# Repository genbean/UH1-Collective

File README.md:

# Heli Collective

A 3D-printed, desk-mounted collective for helicopter flight simulators, modelled on the UH-1 "Huey". It plugs into a PC by USB and shows up as an ordinary game controller, so any sim can use it.

- **The lever** is a 25 mm carbon-fibre tube in a printed base that screws to the desk. It pivots on two ball bearings, a gas strut balances the head's weight, and a knob sets the friction. It travels 32° to a fixed stop. The lever is two-thirds as long as the real one and starts level, so your hand rises about as far as on a real Huey (9.4 in against 9.25 in).
- **The head** is the Huey's collective switch box: GOV RPM, landing light and search light toggles, the SEARCH CONT hat (an 8-way stick), the STOP REL button and the starter trigger. Under it, the twist-grip throttle turns 181° between two hard stops, idle and full open, and stays where you leave it.
- **Sensors:** two AS5600 magnetic angle sensors, one for the lever in the base and one for the throttle in the head. There are no potentiometers to wear out.
- **Electronics:** the HeliSR board, a small PCB that carries a Pro Micro, sits in the head. It reads 16 switch inputs, and the AS5600s over I²C on four sensor ports. Only the USB cable comes out of the base.
- **Software:** the HeliSR firmware and a Windows app, HeliSR Configurator. The app flashes the board, assigns each switch position to a game button and calibrates the axes. Both are based on FreeJoy.

**Interactive exploded views** (point at any part to see what it is): [the base](https://htmlpreview.github.io/?https://github.com/genbean/UH1-Collective/blob/main/Base/renders/rev4_exploded.html), [the base's lever](https://htmlpreview.github.io/?https://github.com/genbean/UH1-Collective/blob/main/Base/renders/rev4_lever_exploded.html), [the head](https://htmlpreview.github.io/?https://github.com/genbean/UH1-Collective/blob/main/Head/renders/HueyHeadR5_Exploded.html), [the head from behind](https://htmlpreview.github.io/?https://github.com/genbean/UH1-Collective/blob/main/Head/renders/HueyHeadR5_Exploded_Rear.html).

More pictures: [from the side](renders/HeliCollective_side.png) and [at the 32° stop](renders/HeliCollective_32deg.png). [`renders/HeliCollective_Assembly.glb`](renders/HeliCollective_Assembly.glb) is the whole collective in 3D; it opens in Windows 3D Viewer or any glTF viewer.

## The parts

Each folder has its own README with the details: how it works, printing, the parts it needs, assembly, and how to rebuild the files.

| Folder | What's in it |
|---|---|
| [`Base/`](Base/README.md) | **MkIII base, Rev 4.** 73 mm (2.87 in) wide, the lever centred on the tube: the pivot on thin-section bearings, the split lever, a shell that encloses it, the gas strut, the brake behind the hub, the stops and the collective's AS5600. Ready-to-print STLs, fit-test coupons, a STEP assembly, renders with every screw labelled, and the scripts that make them. |
| [`Head/`](Head/README.md) | **Huey head, Rev 5.** The switch box in one print, cut to the real UH-1 panels' dimensions, with the throttle grip and its gears, the throttle's AS5600, the starter trigger and the search light hat, and a collision check (`check_r5.py`). STLs and scripts. The BOM lists it. |
| [`PCB/HeliSR/`](PCB/HeliSR/README.md) | **HeliSR Rev 4.0 board.** Sixteen switch inputs, and four I²C ports for the AS5600s, through a PCA9546A switch, in place of the analog inputs. KiCad files, Gerbers, connector pinouts, how to prepare the AS5600 modules, and the assembly order. |
| [`PCB/SearchHat/`](PCB/SearchHat/README.md) | **SearchHat Rev 1.0: the SEARCH CONT hat's breakout board.** An ALPS RKJXM1015004 8-direction stick switch on a 22 × 29 mm board that screws to the lower panel's back, with a JST SH socket or wire pads. KiCad files, Gerbers, the pinout and how to build it. |
| [`BOM/`](BOM) | **The bill of materials for the whole collective:** [`Heli_Collective_BOM.xlsx`](BOM/Heli_Collective_BOM.xlsx): every part to buy, with part numbers, where it goes, where to buy it, how many and the price, and a sheet of the printed parts. [`tools/make_bom.py`](tools/make_bom.py) rewrites it (and checks the board's parts against the board file). |
| [`Software/`](Software/README.md) | **HeliSR firmware and HeliSR Configurator**, with their documentation in [`Software/docs/`](Software/docs) and example profiles, including one for this collective. |
| [`renders/`](renders) | Pictures and a 3D model of the complete collective: head Rev 5 on base Rev 4. [`Base/make_renders_r4.py`](Base/make_renders_r4.py) builds them, and base Rev 4's renders, exploded view and screw chart. [`make_diagrams.py`](renders/make_diagrams.py) draws the head's exploded views, screw maps and screw chart from that model. |

## What you need

The full list, with quantities, part numbers, links and prices, is the [BOM spreadsheet](BOM/Heli_Collective_BOM.xlsx). In outline:

**Electronics**
- The HeliSR Rev 4.0 PCB: send [`HeliSR_Rev4.0_Gerbers.zip`](PCB/HeliSR/HeliSR_Rev4.0_Gerbers.zip) to any PCB maker (2 layers, 39.3 × 33.6 mm).
- The SearchHat Rev 1.0 PCB, for the SEARCH CONT hat: send [`SearchHat_Rev1.0_Gerbers.zip`](PCB/SearchHat/SearchHat_Rev1.0_Gerbers.zip) the same way (2 layers, 22 × 29 mm). Its ALPS switch and JST socket are in the BOM.
- The parts that solder onto it, all from Mouser: the BOM lists them with their board positions.
- A **5 V / 16 MHz Pro Micro** (ATmega32U4). This build uses a USB-C clone; the 3.3 V / 8 MHz version isn't supported.
- Two AS5600 magnetic angle sensor modules, with their magnets.
- JST SR 1.0 mm cables for the board, a 4-core lead for the base's sensor (SDA, GND, VCC, SCL), and a USB-A to USB-C cable. The USB cable runs up through the base and the tube and is spliced inside the head; the BOM's notes explain how.

**Head**
- Four APEM 600H toggle switches, a Same Sky PB4 push button a TE 6 × 6 mm tact switch for the starter trigger, and an ALPS RKJXM1015004 8-way stick switch for the SEARCH CONT hat.
- Four 24 × 2 mm nitrile O-rings, which the throttle grip turns on, a pen spring and four 4 mm board spacers.

**Base**
- Two 6808-2RS thin-section ball bearings (40 × 52 × 7 mm), a 6 in (152 mm), 45 N gas strut with eyelet ends, and a 25 × 23 mm roll-wrapped carbon tube, 500 mm long, used whole.

**Screws, consumables and tools**
- Every screw and nut comes from MonsterBolts in packs of 10, about $23 in all: black-oxide hex socket screws, M2 Phillips flat heads, a stainless M5 hex bolt and plain steel nuts. The BOM and each part's README list them.
- Grease for the bearings and the O-rings, CA glue, hot glue and blue thread-locker; M2, M3, M4 and M5 taps, and 4 mm and 5.2 mm drills for the tube; a soldering iron that can handle 1.0 mm pitch SMD parts.

**Printing and a PC**
- An FDM printer with about 180 mm of build height. The tallest part, the throttle grip, is 173 mm printed upright. The head's panel labels are white, printed in a second filament for the first three layers (an AMS, or a filament change).
- A PC with 64-bit Windows 10 or 11 to set the board up. After that it's a standard USB game controller.
- Python, only if you change the CAD. The STLs are ready to print, and each part's README lists what its scripts need.

## Build order

Each step points to the README that covers it.

1. **Order the parts** from the [BOM](BOM/Heli_Collective_BOM.xlsx), and the PCBs from the Gerbers.
2. **Print the fit-test coupons first**, with the filament and settings you'll use, and try them on your carbon tube, bearings, sensor modules and printed lever dowels: [the base's coupons](Base/README.md#fit-test-coupons) (the 6808 bearing fits, the lever's dowel holes and the tube socket), and the head's O-ring and sensor seat coupons (printed as in [Head, Printing](Head/README.md#printing)). If a fit is off, change its setting in the script and rebuild the STLs.
3. **Build the HeliSR board** ([assembly order](PCB/HeliSR/README.md#assembly-order)) and fit the Pro Micro.
4. **Flash and test it** with HeliSR Configurator: the [quick start](Software/docs/quick-start.md) goes from a bare Pro Micro to a working controller. Check every input now, before it goes into the head. The app picks the HeliSR firmware for you.
5. **Prepare the two AS5600 modules:** remove R1 and R4, wire DIR (to VCC on the base's sensor, to GND on the throttle's), check for about 1 µF on VDD3V3, and measure the module's pull-ups. See the Rev 4.0 board's [AS5600 modules](PCB/HeliSR/README.md#as5600-modules).
6. **Print and assemble the base** ([Base Rev 4, Assembly](Base/README.md#assembly)). The USB cable and the sensor lead go into the lever halves before you close them, the brake strap goes in before the lever, and the tube is drilled, notched and fitted at the end.
7. **Print and assemble the head** ([Head, Assembly](Head/README.md#assembly)): the throttle parts, the starter trigger, the grip on the tube, the head pressed onto the tube, then the board, switches and panels.
8. **Set the two AS5600s' ranges** in HeliSR Configurator's AS5600 helper ([AS5600 guide](Software/docs/as5600.md#setting-the-start-and-stop)): the collective on AX1, the throttle on AX4. The firmware writes each range to its sensor over I²C at every start-up and burns nothing, so it can be set again whenever you like.
9. **Balance and set the friction** ([Base Rev 4, Balance](Base/README.md#balance) and [Brake](Base/README.md#brake)).
10. **Load the UH-1 profile** in HeliSR Configurator, calibrate the axes, and bind the buttons in your sim ([Profiles](Software/docs/profiles.md#uh-1-collective-helisr-head)).

## Status

As of November 2026 the current design is **head Rev 5, base Rev 4 and HeliSR Rev 4.0**.

- **First build:** the first collective was printed and assembled on base Rev 3. What it taught us went into base Rev 4:
  - **Bearings:** the bearing seats fitted perfectly, and the races pressed onto the trunnions a hair too tight.
  - **Strut:** the 45 N strut lifted the lever. Its anchor has since moved, in Rev 4.
  - **Width:** at 130 mm, the base was wider than it needed to be.
- **Base Rev 4:** its first frame, shell and lever were printed and assembled (2026-11-08), and the bearing coupons fitted. Since then it has changed (split lever, brake strap, covers, cable path, lever opening), checked in CAD for collisions and fits through the whole travel and the assembly order; reprint all of it but the strut collar.
- **Head Rev 5:** designed, and checked in CAD for collisions and fits. Earlier head fits were tuned with coupons on an aluminium tube, so check them on the carbon tube.
- **HeliSR Rev 4.0 board:** designed and checked (design rules, and every pad's net against the chips' datasheets), not built yet.
- **Software:** the firmware and HeliSR Configurator in [`Software/`](Software/README.md) support the Rev 4.0 board, with its I²C sensors and their ranges set in the app. They are tested on the PC and a bare Pro Micro only; the Rev 4.0 sensor code against a model of the I²C switch and the AS5600. The software hasn't run on a built board with real switches and sensors.

Expect more changes as the build goes on.

## Credits and licence

- This repository is under the **GNU General Public License v3.0** ([LICENSE](LICENSE)), except where a folder says otherwise.
- **The software in `Software/`** is under the **GNU GPL v3 or later**. It is a modified version of [FreeJoy](https://github.com/FreeJoy-Team/FreeJoy) and [FreeJoyConfiguratorQt](https://github.com/FreeJoy-Team/FreeJoyConfiguratorQt) by the FreeJoy team, ported to the Pro Micro, and isn't made or supported by them. [`Software/NOTICE.md`](Software/NOTICE.md) lists the changes and the third-party components.
- **The original collective: Gazmac52.** This project grew out of [DIY Helicopter Collective Hall Effect](https://www.thingiverse.com/thing:5226353) by **Gazmac52** on Thingiverse, the "MkII" in this project's file names, licensed under [Creative Commons Attribution 4.0](https://creativecommons.org/licenses/by/4.0/). Several components are borrowed from it: the head's throttle grip is built from its grip, modified (`Head/source/MkII-Grip-bore-relieved-25mm.stl`), the HeliSR board reads its switches through 74HC165 shift registers, as Gazmac52's board does, and the head and base are modelled in the MkII's coordinate frames.
- **hotpretzel.** Some components are borrowed from [UH-1 Huey Helicopter Collective](https://www.thingiverse.com/thing:4284120) by **hotpretzel** on Thingiverse, licensed under [Creative Commons Attribution-NonCommercial](https://creativecommons.org/licenses/by-nc/4.0/). The head's faux throttle friction knob is built from hotpretzel's friction knob STL: its wheel profile and flutes were measured off it. So the knob, and the head bodies that carry it (`HueyHeadR4-Body.stl`, `HueyHeadR5-Body.stl` and the scripts' `friction_knob()`), are for **non-commercial use only**, whatever the licence of the folder they're in.
- **Font:** the panels' labels are cut from **Routed Gothic Narrow** by Darren Embry ([webonastick.com/routed-gothic](https://webonastick.com/routed-gothic/)), a digitized Leroy lettering template and the closest free match to the engraved lettering on the real UH-1 panels. It's bundled in [`fonts/routed-gothic/`](fonts/routed-gothic) under the [SIL Open Font License 1.1](fonts/routed-gothic/LICENSE.md), so the panels rebuild on any system.
- **The real UH-1's dimensions:** **Kornskydiver**'s caliper photos of a real UH-1 head (2017) and **dcval**'s scaled drawing of its panels (2025), from the ED Forums thread [Huey Collective Measurements](https://forum.dcs.world/topic/152333-huey-collective-measurements/). Head Rev 5 is built to them. Copies are in [`Head/reference/`](Head/reference/README.md), with credit; they belong to their authors and aren't covered by this repository's licence.

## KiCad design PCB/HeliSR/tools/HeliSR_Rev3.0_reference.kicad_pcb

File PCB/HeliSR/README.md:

# HeliSR Rev 4.0 – Pro Micro + I²C collective board (Huey head)

> **Designed, not ordered, not built.** The HeliSR firmware has a Rev 4.0 build and HeliSR Configurator supports
> the board, but neither has run on one yet. See [Firmware](#firmware).

A small carrier board for the collective's switch box: a **SparkFun Pro Micro 5V/16 MHz** with **16 switch
inputs** read through two 74HC165 shift registers, and **four I²C ports for AS5600 magnetic angle
sensors**.

The board reads each AS5600's angle digitally over I²C, which doesn't pick up noise on a long cable the way an
analog output does. Every AS5600
has the same I²C address (0x36), so a **PCA9546A I²C switch** on the back of the board gives each port its own
channel, and the firmware talks to one sensor at a time. Each port has its own 2.2 kΩ pull-ups, and all four
ports are built the same, so any port takes a short or a long cable.

| | |
|---|---|
| Board size | 39.3 × 33.64 mm (1.55 × 1.32 in), with four M3 holes. 2 layers, 1.6 mm FR4 |
| Parts | Connectors, the button, the Pro Micro sockets, the shift registers and their parts on the **front**; the I²C switch, its capacitor and all the resistors on the **back**. Every resistor and capacitor is **1206**, for hand soldering |
| Switch inputs | 16, on two 10-pin JST SR/SH 1.0 mm connectors (BM10B-SRSS-TB, SMD) |
| AS5600 ports | 4, each on its own 4-pin JST SR/SH 1.0 mm connector (BM04B-SRSS-G-TB, SMD): **1 SDA, 2 GND, 3 VCC, 4 SCL** |
| I²C switch | PCA9546A (TI PCA9546ADR, SOIC-16 narrow), address 0x70, with its /RESET on a Pro Micro pin |
| Pull-ups | 2.2 kΩ on SDA and SCL of each port (R1–R8); 10 kΩ on the Pro Micro's SDA and SCL (R9, R10) and on /RESET (R11) |
| Button | **RST** (SW1, E-Switch TL1015AF160QG). No PROG buttons: over I²C the firmware sets each sensor's range itself |
| Ground | Both layers poured with ground and stitched together (see [Checks](#checks-done-on-this-revision)) |
| Fab specs | Cheap-fab rules: 0.2 mm clearance, 0.2 mm signal and 0.3 mm VCC/GND tracks, 0.6/0.3 mm vias, holes at least 0.6 mm apart |

Pots and Hall sensors can't go on the AX ports. The Pro Micro still has analog-capable pins free (A2, A3,
4, 6, 8, 9, 10); using one means soldering a wire to the Pro Micro.

## Layout

Viewed from the top, with the USB end on the left:

- **Pro Micro** on two 12-pin sockets, its USB end at the left edge: pins 13–24 (J8) along the top, pins 1–12
  (J7) along the bottom.
- **Under it**: RN1, then C1 | U1 | C3 | U2 | C2, then RN2.
- **Top edge:** J1 (inputs 1-8), AX3 (J13).
- **Bottom edge:** J2 (inputs 9-16), AX1 (J11).
- **Far end (right):** AX4 (J14, top), RST (SW1, middle), AX2 (J12, bottom).
- **Back:** U3 under the far half of the Pro Micro with C4 beside its VCC pin, R9 and R10 beside its SDA and SCL,
  R11 beside its /RESET; under each port, that port's pair of pull-ups.

Every connector's pins face the board's middle. The JST plugs go in from the top and the cables leave upwards.

Mounting hole centres, in mm from the board's top-left corner (USB end left, J1 up): (3.2, 3.2), (36.1, 3.2),
(3.2, 30.44) and (36.1, 30.44).

## In the Huey head

It fits head Rev 4 and Rev 5 on their spacers and screws. The parts on its front are JST SH height (head Rev 5's
`check_r5.py` takes them as 4.5 mm); the parts on its back (1.75 mm at most) sit in the 4 mm gap the spacers leave
behind the board.

Two things to allow for:
- **AX4 and AX2 are at the far end**: the top of the board in the head, just below the upper
  box's toggles. Their plugs go in from the front, like the others. Leave the wires room to turn there.
- **The throttle's AS5600 needs four wires**, and so does the collective's, which runs up the tube
  from the MkIII base (`Base`). Check the wire channels take four wires.

## Connectors

**J1 (inputs 1-8) and J2 (inputs 9-16)**: 10-pin JST SR/SH 1.0 mm.

| Pin | 1 | 2 | 3 | 4 | 5 | 6 | 7 | 8 | 9 | 10 |
|---|---|---|---|---|---|---|---|---|---|---|
| J1 | GND | IN1 | IN2 | IN3 | IN4 | IN5 | IN6 | IN7 | IN8 | GND |
| J2 | GND | IN9 | IN10 | IN11 | IN12 | IN13 | IN14 | IN15 | IN16 | GND |

Each switch goes between its input pin and GND. The inputs have 10 kΩ pull-ups on the board.

**AX1–AX4 (J11–J14)**: 4-pin JST SR/SH 1.0 mm.

| Pin | 1 | 2 | 3 | 4 |
|---|---|---|---|---|
| AX1–AX4 | SDA | GND | VCC (5 V) | SCL |

The order keeps SDA and SCL apart, with GND beside SDA and VCC beside SCL, which is what you want on a long cable:
twist SDA with GND and SCL with VCC, or use a 4-core cable with those pairs. It is **not** the Qwiic / STEMMA QT
order, on purpose: those boards are 3.3 V and this port is 5 V.

If you make a lead by cutting a pre-made JST SR/SH jumper in half, find which wire is pin 1 with a meter before
soldering the sensor end: the plug is keyed, but the wires may all be one colour.

| Port | Connector | PCA9546A channel | Pull-ups (SDA, SCL) | Suggested use |
|---|---|---|---|---|
| AX1 | J11 | 2 | R1, R2 | Collective (AS5600 in the MkIII base) |
| AX2 | J12 | 1 | R3, R4 | Spare |
| AX3 | J13 | 3 | R5, R6 | Spare |
| AX4 | J14 | 0 | R7, R8 | Throttle (AS5600 in the Huey head) |

The channels follow the board's geometry, not the port numbers: the firmware maps them.

## The I²C circuit

```
Pro Micro "2" SDA ──┬── R9 10k ── VCC                    ┌── R(odd) 2.2k ── VCC
Pro Micro "3" SCL ──┼── R10 10k ── VCC        PCA9546A   ├── port pin 1 SDA ─── AS5600 SDA
Pro Micro "A1" ─────┴── R11 10k ── VCC   ──── SDA/SCL ── SDn/SCn (n = 0..3) ── port pin 4 SCL ─── AS5600 SCL
                                         /RESET, A0-A2 = GND (0x70)           └── R(even) 2.2k ── VCC
```

- **Address:** A0–A2 are tied to GND, so the switch is at **0x70**; the AS5600s are at 0x36 behind it.
- **One channel at a time:** the firmware writes the switch's control register to connect one port, reads that
  sensor, and moves on. Only that port's cable is on the bus, so the long cables don't add up.
- **Pull-ups:** each port has its own 2.2 kΩ pair, on the switch's side of its cable, so each channel is a complete
  I²C bus whether or not the sensor module has pull-ups. With the Pro Micro's 10 kΩ pair in parallel, a low SDA
  sinks 2.3 + 0.5 = 2.8 mA at 5 V, plus whatever the module's own pull-ups add. The weakest part on the bus is the
  PCA9546A, and only while it acknowledges its own writes: TI rates it to sink at least 3 mA at 0.4 V and 6 mA at
  0.6 V (SCPS148I). Every input on the bus reads below 1.5 V (0.3 × 5 V) as low, so anything up to 6 mA works with
  margin. The AS5600 sinks 20 mA at 0.4 V (ams datasheet v1-06), the ATmega32U4 more.
- **/RESET:** R11 holds it high, so the switch works even before the firmware drives A1. Pulling A1 low resets the
  switch (all channels off), which frees a stuck bus. R11 goes to the same 5 V as the chip, as TI's errata ask.
- **Clock speed:** the AS5600 runs up to 1 MHz, but long cables want a slow clock. Plan on **100 kHz**, and less
  (50 or 25 kHz) if a long cable gives errors. Even at 25 kHz, reading all four sensors takes about 10 ms. The clock
  is set in the firmware, not on the board.
- **Cable length:** the limit is the capacitance on each line: 400 pF in the I²C standard (the AS5600 allows
  550 pF). Typical 4-core cable is 50–150 pF per metre, so a metre or more is within it. With 2.2 kΩ and 200 pF
  the rise time is about 0.4 µs, well inside 100 kHz's 1 µs.

## AS5600 modules

For the common WWZMDiB module (23 × 23 mm, Amazon B0CM3C8KFT), running on the Pro Micro's 5 V:

The R numbers in this list are the module's, not the board's. The pin facts are from the AS5600 datasheet (ams
v1-06); which part on the module is R1 or R4 is from the module itself, so check yours.

- **Remove the module's R1**, the 0 Ω link between VDD5V and VDD3V3: it puts 5 V on the chip's
  3.3 V pin, whose absolute maximum is 4.0 V. The two pins are tied together only when the chip runs on 3.3 V.
- **Check there is about 1 µF from VDD3V3 to GND.** On 5 V, VDD3V3 is the output of the chip's internal regulator,
  and the datasheet asks for a 1 µF low-ESR ceramic there. A module built to run on 3.3 V through R1 may have only
  100 nF on that pin, or nothing. If so, add a 1 µF ceramic between VDD3V3 and GND.
- **Wire DIR** to GND or VCC (it floats on this module, and the chip has no pull on it). Over I²C it still sets
  which way the angle rises (GND = clockwise, seen from the chip's top face); the firmware can invert an axis
  either way.
- **Remove the module's R4**, the 1 kΩ from PGO (GPO on the module) to GND. With it fitted PGO is low, which
  selects OUT-pin programming. In that mode, pulling OUT to GND for 100 ms twice burns the
  range into the chip for good, which can be done only once; a stray short on OUT could do it by accident. Without
  R4 the chip's internal pull-up holds PGO high and OUT is just an output. Leave OUT unconnected.
- **Wire VCC, GND, SDA and SCL** to the port: pin 1 SDA, 2 GND, 3 VCC, 4 SCL.
- **Check the module's own pull-ups.** The AS5600 has none of its own; the module may add some (ams suggests
  4.7 kΩ). With the module unpowered and unplugged, measure the resistance from SDA to VCC and from SCL to VCC. The
  limit is the 6 mA in [The I²C circuit](#the-i²c-circuit):
  - **Open circuit (no reading):** no pull-ups. Fit 2.2 kΩ for the board's R1–R8 as listed.
  - **10 kΩ or 4.7 kΩ:** fine; with the board's 2.2 kΩ the bus sinks 3.3 or 3.8 mA. They also speed up the
    rising edges on a long cable. Leave them, and fit R1–R8 as listed.
  - **Under 2 kΩ:** too strong together with 2.2 kΩ. Remove the module's two pull-ups.
  - Check also that the module's pull-ups go to VCC, not to the chip's 3.3 V pin; if they read open to VCC but
    about the same value to VDD3V3, remove them, as they'd push current from the 5 V bus into the chip's regulator.

Nothing is burnt into the chip: the firmware writes each sensor's start and stop angles (ZPOS, MPOS) to its
working registers every time it starts, so the range can be changed as often as you like.

## Pro Micro pins

| Socket pin | Pro Micro pin | Port | Use |
|---|---|---|---|
| 5 | 2 | PD1 | I²C SDA |
| 6 | 3 | PD0 | I²C SCL |
| 15 | 14 | PB3 | Shift register data (U2 QH) |
| 16 | 15 | PB1 | Shift register clock |
| 17 | A0 | PF7 | Shift register load (SH/LD) |
| 18 | A1 | PF6 | PCA9546A /RESET |
| 21, 22, 3/4/23 | VCC, RST, GND | | |

Spare (not connected): TX, RX, 4, 5, 6, 7, 8, 9, 10, 16, A2 and A3. The shift-register pins are the hardware SPI
clock (15) and MISO (14), so a future firmware can read the chain with the SPI unit; pin 16 (MOSI) is then not
free for other use.

## Firmware

The HeliSR firmware in `Software/firmware/HeliSR` is built for this board by `Software/firmware/build.ps1`,
shipped as `firmware\HeliSR_Rev4.0_16MHz.hex`. It:

- reads the shift registers on pins 14 (data), 15 (clock) and A0 (load);
- runs the TWI on pins 2 and 3 at 100 kHz, or 50, 25 or 10 kHz for long cables (set in HeliSR Configurator), connects
  one port's PCA9546A channel at a time and reads its AS5600's ANGLE register (address 0x36), scaled to the analog
  inputs' 0–4092. It also reads STATUS, RAW ANGLE and AGC, for the magnet checks and the Configurator's helper;
- writes each sensor's start and stop to its volatile ZPOS and MPOS at start-up, 1 ms apart, from settings it keeps
  in EEPROM (the Configurator sets them), and CONF as 0 (the chip's factory settings, over anything burnt in); reads
  them back, and writes them again to a sensor that comes back after an error or has lost them. It never burns
  anything;
- maps channels 2, 1, 3, 0 to AX1–AX4 as above. A stuck bus is freed by pulling A1 low (never driving it high), clocking
  out a half-sent byte and sending a STOP; a port that stuck it is left alone for 250 ms;
- treats A2 and A3 as spare analog pins (axis sources 9 and 10), and leaves pin 14 out of the
  spare pins;
- sets the JTD bit in MCUCR at start-up (written twice, as the ATmega32U4 requires). A0 and A1 are also the JTAG
  pins TDI and TDO (PF7, PF6); SparkFun ships the Pro Micro with JTAG off in its fuses (high fuse 0xD8), but a clone
  with JTAG on would otherwise keep both pins from working as plain I/O.

The sensor code is tested on a PC against a model of the PCA9546A and the AS5600 (`Software/firmware/test/host`).
Nothing of this board's firmware has run on the board itself: the shift-register pins, the I²C timing on real
cables, the bus recovery and the sensors' behaviour all wait for one. `Software/PLAN.md` lists what's still to check.

**Only this board.** The firmware is for Rev 4.0 only. Every build carries a tag saying so, INFO reports it, and HeliSR Configurator refuses a `.hex` tagged for another board and asks before flashing an untagged one or a Pro Micro whose firmware reports another board.

## Files

| File | What it is |
|---|---|
| `HeliSR_Rev4.0.kicad_pcb` / `.kicad_pro` | KiCad 9 board |
| `HeliSR_Rev4.0.kicad_dru` | Custom DRC rules for the intentional overlaps (see below) |
| `HeliSR.pretty/`, `fp-lib-table` | Project footprint library: the TL1015AF160QG button footprint |
| `HeliSR_Rev4.0_Gerbers.zip` | Gerbers + drill files |
| `HeliSR_Rev4.0_Top.png`, `HeliSR_Rev4.0_Bottom_mirrored.png` | Board renders |
| `HeliSR_Rev4.0_Input_Map.csv` | Every input → connector pin → chip pin → shift order |
| `tools/` | The scripts that build, route, finish, check and export this board (see Rebuilding) |

## Assembly order

1. **The back first**, while the front is still flat: **U3** (pin 1 dot toward the far end, at the J1 side), then
   **C4** and **R1–R11** (all 1206). R1–R8 are all 2.2 kΩ; R9–R11 10 kΩ.
2. On the front, **U1, U2**, then the 1206 caps **C1, C2, C3**.
3. **RN1, RN2**. The dot (pin 1) goes in the square pad.
4. The JST headers and the RST button.
5. The two Pro Micro sockets last. Use low-profile headers for the sockets and for the Pro Micro's pins (the BOM lists a set): standard ones stand too tall for the USB cable in the head.

## Pro Micro RP2040 compatibility

Every pin the board uses is also there on the **SparkFun Pro Micro RP2040**, whose VCC pin is 3.3 V:
its pins 2 and 3 (GPIO2, GPIO3) can be the RP2040's I2C1 SDA and SCL, and the pull-ups then go to 3.3 V, which suits an AS5600 module
run in its 3.3 V mode (R1 left fitted). There is no RP2040 build of the HeliSR firmware. Not tried.

## DRC rules

`HeliSR_Rev4.0.kicad_dru` covers the intentional overlaps, each rule naming the exact footprint pairs:

- Parts nested under the Pro Micro (resistor networks, shift registers and caps between the sockets).
- The connector rows: the courtyards of J1 and AX3 (J13), and of J2 and AX1 (J11), overlap; the housings don't.
- The M3 holes: their courtyards (6.9 mm across) overlap J1, J2 and the far-end ports AX4 (J14) and AX2 (J12). Every
  pad, track and via is at least 3.5 mm from each hole centre, clear of the M3 nut's corners (3.18 mm) on the front
  and the 6.4 mm spacer on the back.
- The far end: RST's courtyard overlaps the AX4 and AX2 ports' by up to 0.3 mm; the switch body and the JST housings
  are about 1.4 mm apart.
- Library silkscreen outlines that touch where parts nest.

The rules use `(severity ignore)`, because `kicad-cli` 9.x still reports `(severity exclusion)` rules as errors
(KiCad issue 24264).

## Rebuilding

The board is generated, autorouted and finished by scripts in `tools/`, run with KiCad 9 (its own Python, which has
numpy and PIL) and Freerouting 2.5.0 on a Java 25 runtime. No other Python packages are needed. The board's parts are in
the collective's BOM, [`../../BOM`](../../BOM).

1. `gen_v4.py` places the parts, sets the nets, outline and mounting holes, and exports a DSN. The placement used
   here is `rev40_params.json`.
2. `route_v4.py` runs the generator for a list of placement variants, gives VCC/GND a 0.3 mm class, routes with
   Freerouting, imports the result (`imp_v2.py`) and DRCs it. It routes with the vias 0.7 mm across, so their holes
   end up at least 0.6 mm apart, and imports them at 0.6 mm. This board is the best of the 45 variants in the final sweep
   (U3's position, the pull-ups' offset under the ports, the far-end ports' spacing): complete, 44 router vias.
3. `finish_all_v4.py` widens the router's neck-downs, pours GND on both layers, adds GND stitching vias
   (`stitch_v4.py`), writes the DRC rules and title block (`finish_v4.py`), places the silk labels on both sides
   (`silk_fix_v4.py`), and DRCs the result.
4. `verify_netlist_v4.py` checks the netlist against the reference board and input map kept in `tools/` for it, and
   against the PCA9546A datasheet's pinout, and writes the input map.
5. `export_v4.py` writes `HeliSR_Rev4.0_Gerbers.zip` and the two renders. `tools/make_bom.py` (at the repo root) then rewrites the
   BOM (it stops if the board's parts and its list disagree).

## Checks done on this revision

- **KiCad 9 DRC:** 0 violations and 0 unconnected items at every severity (with `HeliSR_Rev4.0.kicad_dru`).
- **Netlist:** checked pad by pad by `verify_netlist_v4.py`. J1, J2, U1, U2, RN1, RN2, C1–C3 and SW1 are on the
  same nets as in the reference board, so the inputs and their shift order are unchanged. U3's pins match the
  PCA9546A datasheet (TI SCPS148I): A0 1, A1 2, /RESET 3, SD0–SC1 4–7, GND 8, SD2–SC3 9–12, A2 13, SCL 14, SDA 15,
  VCC 16. Every port, pull-up and Pro Micro pin is as listed above, and every net joins at least two pads.
- **Clearance:** the cheap-fab rules above. All copper is at least 0.5 mm from the edge, and every track and via at
  least 3.7 mm from a hole centre (every pad 4.1 mm). No neck-downs: every signal track is 0.2 mm and every VCC/GND
  track 0.3 mm.
- **Routing:** 998 mm of track, 78 vias: 44 from the router and 34 GND stitching vias. The I²C lines from U3 to the
  ports are 6–29 mm long.
- **Decoupling:** C4's VCC pad is 2.65 mm from U3's VCC pin (centre to centre); C1's is 1.8 mm from U1's and C2's
  2.7 mm from U2's.
- **Silkscreen:** every label is 1.0 mm tall with a 0.16 mm stroke, outside every courtyard on its side, and at least
  0.5 mm from the next label. The front names the connectors (J1, J2, AX1–AX4), RST, USB and the front parts; the
  back names U3, C4, R1–R11 and the board.
- **Not checked:** nothing has been built. The I²C circuit and the cable lengths are as calculated in the
  I²C section above, not measured.

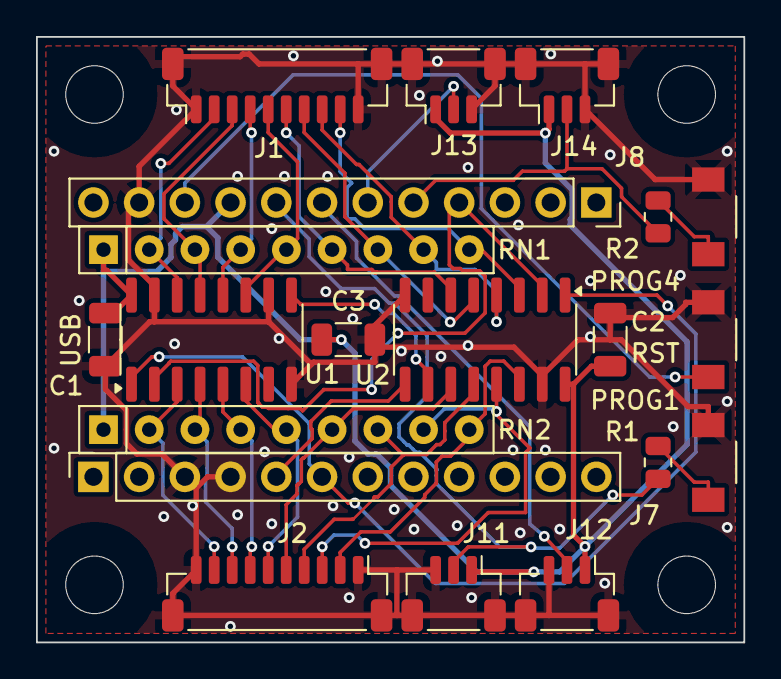
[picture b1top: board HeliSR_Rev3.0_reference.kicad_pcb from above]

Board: 2 copper layers, 39.3 x 33.6 mm, 24 parts (0 on the bottom side), 29 nets.

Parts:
C1, C2: 100nF; C_1206_3216Metric
C3: 22uF; C_1206_3216Metric
H1, H2, H3, H4: M3; MountingHole_3.2mm_M3
J1: Inputs 1-8; JST_SH_BM10B-SRSS-TB_1x10-1MP_P1.00mm_Vertical
J2: Inputs 9-16; JST_SH_BM10B-SRSS-TB_1x10-1MP_P1.00mm_Vertical
J7: Pro Micro pins 1-12; PinSocket_1x12_P2.54mm_Vertical
J8: Pro Micro pins 13-24; PinSocket_1x12_P2.54mm_Vertical
J11: AX1; JST_SH_BM03B-SRSS-TB_1x03-1MP_P1.00mm_Vertical
J12: AX2; JST_SH_BM03B-SRSS-TB_1x03-1MP_P1.00mm_Vertical
J13: AX3; JST_SH_BM03B-SRSS-TB_1x03-1MP_P1.00mm_Vertical
J14: AX4; JST_SH_BM03B-SRSS-TB_1x03-1MP_P1.00mm_Vertical
R1, R2: 1k; R_0805_2012Metric
RN1, RN2: 10k x8 bussed; R_Array_SIP9
SW1, SW2, SW3: TL1015AF160QG; SW_TL1015AF160QG
U1, U2: 74HC165; SOIC-16_3.9x9.9mm_P1.27mm

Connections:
AX1: J8.20, J11.2, R1.1
AX2: J8.19, J12.2
AX3: J8.18, J13.2
AX4: J8.17, J14.2, R2.1
GND: C1.2, C2.2, C3.2, J1.1, J1.10, J1.MP, J2.1, J2.10, J2.MP, J7.3, J7.4, J8.23, J11.3, J11.MP, J12.3, J12.MP, J13.3, J13.MP, J14.3, J14.MP, SW1.2, SW2.2, SW3.2, U1.8, U1.10, U1.15, U2.8, U2.15
IN1: J1.2, RN1.2, U1.14
IN2: J1.3, RN1.3, U1.13
IN3: J1.4, RN1.4, U1.12
IN4: J1.5, RN1.5, U1.11
IN5: J1.6, RN1.6, U2.6
IN6: J1.7, RN1.7, U2.5
IN7: J1.8, RN1.8, U2.4
IN8: J1.9, RN1.9, U2.3
IN9: J2.2, RN2.9, U2.14
IN10: J2.3, RN2.8, U2.13
IN11: J2.4, RN2.7, U2.12
IN12: J2.5, RN2.6, U2.11
IN13: J2.6, RN2.5, U1.6
IN14: J2.7, RN2.4, U1.5
IN15: J2.8, RN2.3, U1.4
IN16: J2.9, RN2.2, U1.3
PROG1: R1.2, SW2.1
PROG4: R2.2, SW3.1
RST: J8.22, SW1.1
SR_CHAIN: U1.9, U2.10
SR_CLK: J8.16, U1.2, U2.2
SR_DATA: J7.5, U2.9
SR_LOAD: J7.6, U1.1, U2.1
VCC: C1.1, C2.1, C3.1, J8.21, J11.1, J12.1, J13.1, J14.1, RN1.1, RN2.1, U1.16, U2.16

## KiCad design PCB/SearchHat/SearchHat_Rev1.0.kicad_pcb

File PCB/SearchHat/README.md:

# SearchHat Rev 1.0: breakout board for the SEARCH CONT hat

A small board for hat Rev 4 in the Huey head Rev 5 ([`Head/Hat`](../../Head/Hat/README.md)). It carries an **ALPS RKJXM1015004** 8-direction stick switch with a centre push, and screws to four bosses printed on the back of the lower panel. The switch's body comes through the panel's 13.5 mm hole and the cap goes on its stick.

| Front: faces the panel | Back, mirrored: as you see it from behind |
|---|---|
|  |  |

| | |
|---|---|
| Size | 22 × 29 mm, 2 layers, 1.6 mm FR4, 2 mm corners |
| Holes | Four 2.2 mm holes for M2 × 8 countersunk screws, 8.5 mm from the switch's centre each way (17 mm apart). Every track and both ground pours stop 2.2 mm from each hole's centre, clear of the 3.8 mm screw head |
| Switch | SW1, on the front, centred 11 mm from each long side and 14 mm below the top edge |
| Connector | J1, a 6-pin JST SH 1.0 mm side-entry header (SM06B-SRSS-TB), on the back at the top. The plug goes in from the top edge and the cable leaves upward |
| Wire pads | J2, six 2 mm-pitch plated holes (0.8 mm) along the bottom, to solder wires to instead of J1 |
| Ground | Pours on both sides, joined by eight vias |

## The switch

The RKJXM1015004 has nine pins on two circles (9.9 and 10.7 mm) and a 1.1 mm locating peg. The footprint (`SearchHat.pretty/SW_ALPS_RKJXM1015004`) takes its pin centres from JLCPCB/EasyEDA's footprint for the part (LCSC C97432), which match the ALPS catalog's mounting-hole drawing: 1.0 mm holes for the pins, here with 1.6 mm pads, and a 1.2 mm unplated hole for the peg.

How it's wired inside, from the catalog's circuit diagram:
- **PUSH** (three pins, joined inside) is the common of the four directions. Tilting the stick joins PUSH to A, B, C or D; a diagonal joins two neighbours, so it's an 8-way switch.
- The **centre push** joins COM to PUSH.
- **GND** is the metal frame.

So the board ties PUSH and GND to ground. A–D are the four directions and COM is the centre push. Seen from the front (as you look at the panel), and going by the catalog's lever drawing: **A is up (EXT), C down (RETR), B left (L) and D right (R)**. The silkscreen on the front has an arrow marked EXT pointing up.

## Pinout

| Signal | Switch pin | J1 pin | J2 pad | HeliSR J2 pin | HeliSR input |
|---|---|---|---|---|---|
| R (right) | D | 1 | 1 | 5 | IN12 |
| GND | PUSH ×3, GND | 2 (and the mounting tabs) | 3 | 1 or 10 | |
| RETR (down) | C | 3 | 2 | 3 | IN10 |
| CTR (centre push) | COM | 4 | 5 | 8 | IN15 (spare; leave it off if you don't want a centre button) |
| EXT (up) | A | 5 | 4 | 2 | IN9 |
| L (left) | B | 6 | 6 | 4 | IN11 |

These are the inputs the tact-switch hats used (IN9–IN12 as EXT, RETR, L, R), so the existing profiles work as they are. The centre push is new. IN15 is spare, so bind it in a profile if you want it.

The pin order isn't GND first. On J1 the signals follow the order their switch pins come round the ring, so every track on the back runs without a crossing; on J2 the same goes for the front. The silkscreen names them:
- **J1:** "1" and "6" mark its ends on the back. Up the long edges, "J1: 1R 2GND 3RETR" and "J1: 4CTR 5EXT 6L". Seen from behind, pin 1 is on the right.
- **J2:** each pad's name is under it, on both sides.

**The lead:** cut a 6-pin JST SH jumper (A06SR06SR30K203A) in half, as for the HeliSR's ports. Plug one end into J1 and splice its wires into the HeliSR's J2 loom as in the table. Check pin 1 with a meter: cut jumpers come in both "same side" and "reversed" versions. Or leave J1 off and solder five or six wires to J2.

## Building it

1. **J1 first**, on the back, while the board is flat. Line its pins up on the pads, then tack and solder the two mounting tabs.
2. **SW1** on the front: its peg goes in the 1.2 mm hole, so it only fits one way. Hold it flat against the board and solder its nine pins on the back. It must sit flat: it is what places the stick in the panel's hole.
3. Check with a meter, with nothing pressed: no direction or CTR is joined to GND. Tilt each way and press the middle: each joins its own signal to GND, and each diagonal joins two.

Fitting it to the panel and the cap: [the hat](../../Head/Hat/README.md).

## Checks

- **DRC:** `kicad-cli pcb drc` reports no violations and nothing unconnected. The rules are the HeliSR boards' cheap-fab rules: 0.127 mm minimum track and clearance, with this board's net class at 0.3 mm tracks and 0.2 mm clearance. Two exceptions are written into `SearchHat_Rev1.0.kicad_dru`, each limited to the parts it names:
  - The lower M2 holes' library courtyards overlap J2's by about 0.5 mm. The screw head itself is 0.9 mm from the nearest pad.
  - The left PUSH pin gets one thermal spoke on the back, where R runs past it. A ground track on the back and the front pour join it as well.
- **Fit in the head:** `Head/check_r5.py` places the board, the switch, J1 and a plug with its wires against the body, the toggles and the HeliSR board: all clear. The tightest spot is the end of J1's plug, 2.2 mm below the lower box's top wall. From about 12 mm behind the panel the slot up to the upper box is open, so the wires turn straight back and go up to the HeliSR.

## Not checked

Nothing is ordered or built yet. Still to check on a real part:
- the footprint, against the switch itself: the pin centres come from two sources that agree, but neither is ALPS's own PCB drawing;
- that A is really up, as the catalog's lever drawing reads. If a direction comes out wrong, swap its inputs in the profile, or swap the wires;
- whether a countersunk M2 head sits well on the board's plain 2.2 mm hole. A small washer under each head is fine if it doesn't.

## Files

| File | What it is |
|---|---|
| `SearchHat_Rev1.0.kicad_pcb`, `.kicad_pro`, `.kicad_dru` | The board, its project and its rules (KiCad 9) |
| `SearchHat.pretty/` | The switch's footprint |
| `SearchHat_Rev1.0_Gerbers.zip` | Gerbers with Protel extensions and a job file, plus the PTH and NPTH drill files: send it to any PCB maker |
| `SearchHat_Rev1.0_Top.png`, `_Bottom_mirrored.png` | The pictures above |
| `SearchHat_Rev1.0_mech.json` | The outline, holes and parts' places, measured from the switch's centre. `Head/Hat/hat4_r5.py` reads it, so the panel's bosses always match the board |
| `tools/gen_searchhat.py` | Builds the board from scratch: parts, hand-placed tracks, pours, silkscreen, rules and the JSON |
| `tools/export_searchhat.py` | Writes the Gerbers and the pictures (the HeliSR's export script, sized for this board) |

## Rebuilding

From this folder:

```bash
"$LOCALAPPDATA/Programs/KiCad/9.0/bin/python.exe" tools/gen_searchhat.py .
```

```bash
"$LOCALAPPDATA/Programs/KiCad/9.0/bin/kicad-cli.exe" pcb drc --severity-all --format json -o drc.json SearchHat_Rev1.0.kicad_pcb
```

```bash
python tools/export_searchhat.py SearchHat_Rev1.0.kicad_pcb .
```

Then, in `Head/Hat`, run `python hat4_r5.py ../stl` so the panel's bosses follow any change.

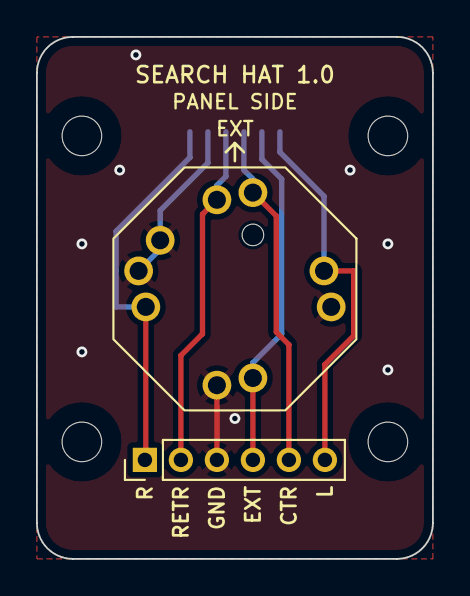
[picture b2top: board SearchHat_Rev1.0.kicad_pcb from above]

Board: 2 copper layers, 22.0 x 29.0 mm, 7 parts (1 on the bottom side), 6 nets.

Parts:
H1, H2, H3, H4: M2; MountingHole_2.2mm_M2
J1: JST SM06B-SRSS-TB; JST_SH_SM06B-SRSS-TB_1x06-1MP_P1.00mm_Horizontal
J2: Wire pads, 2 mm; PinHeader_1x06_P2.00mm_Vertical
SW1: ALPS RKJXM1015004; SW_ALPS_RKJXM1015004

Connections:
CTR: J1.4, J2.5, SW1.1 (COM)
EXT: J1.5, J2.4, SW1.2 (A)
GND: J1.2, J1.MP, J2.3, SW1.6 (PUSH), SW1.7 (GND)
L: J1.6, J2.6, SW1.3 (B)
R: J1.1, J2.1, SW1.5 (D)
RETR: J1.3, J2.2, SW1.4 (C)
